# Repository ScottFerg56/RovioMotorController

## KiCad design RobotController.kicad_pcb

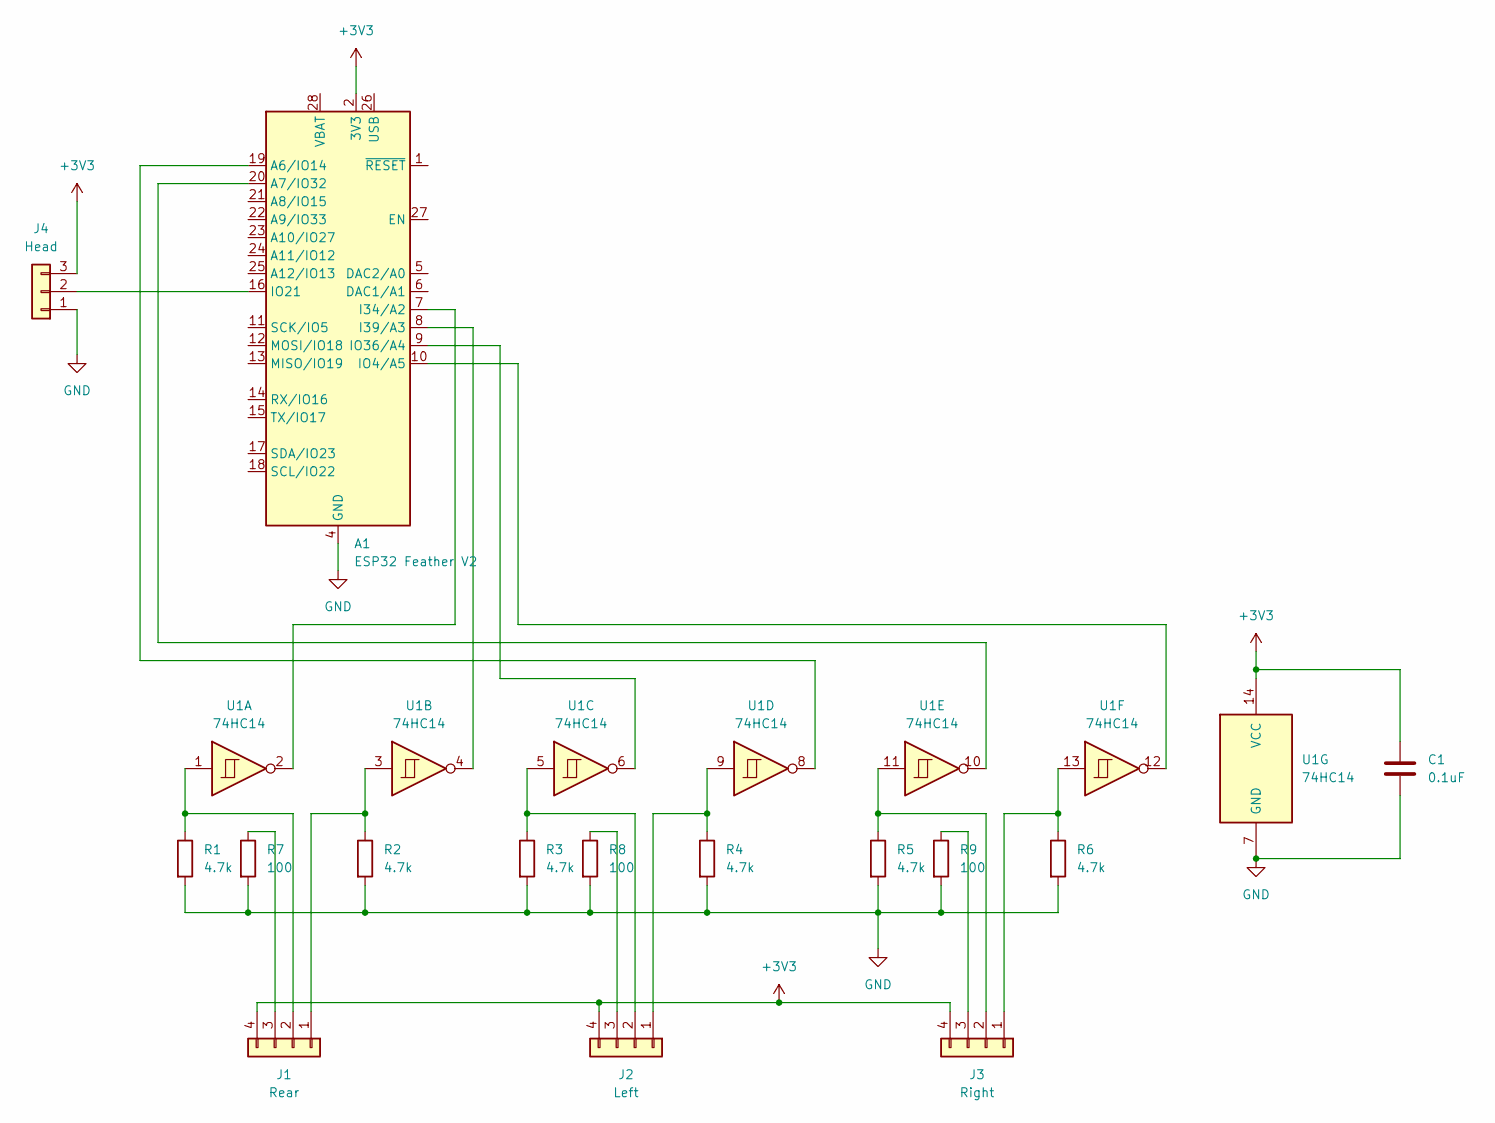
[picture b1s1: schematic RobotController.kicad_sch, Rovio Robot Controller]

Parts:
A1: ESP32 Feather V2; Adafruit_Feather
C1: 0.1uF; C_0805_2012Metric_Pad1.18x1.45mm_HandSolder
J1: Rear; JST_PH_B4B-PH-K_1x04_P2.00mm_Vertical
J2: Left; JST_PH_B4B-PH-K_1x04_P2.00mm_Vertical
J3: Right; JST_PH_B4B-PH-K_1x04_P2.00mm_Vertical
J4: Head; JST_PH_B3B-PH-K_1x03_P2.00mm_Vertical
R1, R2, R3, R4, R5, R6: 4.7k; R_0805_2012Metric_Pad1.20x1.40mm_HandSolder
R7, R8, R9: 100; R_0805_2012Metric_Pad1.20x1.40mm_HandSolder
U1: 74HC14; SOIC-14_3.9x8.7mm_P1.27mm

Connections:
+3V3: A1.2 (3V3), C1.1, J1.4, J2.4, J3.4, J4.3, U1.14 (VCC)
GND: A1.4 (GND), C1.2, J4.1, R1.2, R2.2, R3.2, R4.2, R5.2, R6.2, R7.2, R8.2, R9.2, U1.7 (GND)
unnamed: A1.19 (A6/IO14), U1.8
unnamed: A1.20 (A7/IO32), U1.10
unnamed: A1.7 (I34/A2), U1.2
unnamed: A1.8 (I39/A3), U1.4
unnamed: A1.10 (IO4/A5), U1.12
unnamed: A1.16 (IO21), J4.2
unnamed: A1.9 (IO36/A4), U1.6
unnamed: J1.1, R2.1, U1.3
unnamed: J1.2, R1.1, U1.1
unnamed: J1.3, R7.1
unnamed: J2.1, R4.1, U1.9
unnamed: J2.2, R3.1, U1.5
unnamed: J2.3, R8.1
unnamed: J3.1, R6.1, U1.13
unnamed: J3.2, R5.1, U1.11
unnamed: J3.3, R9.1

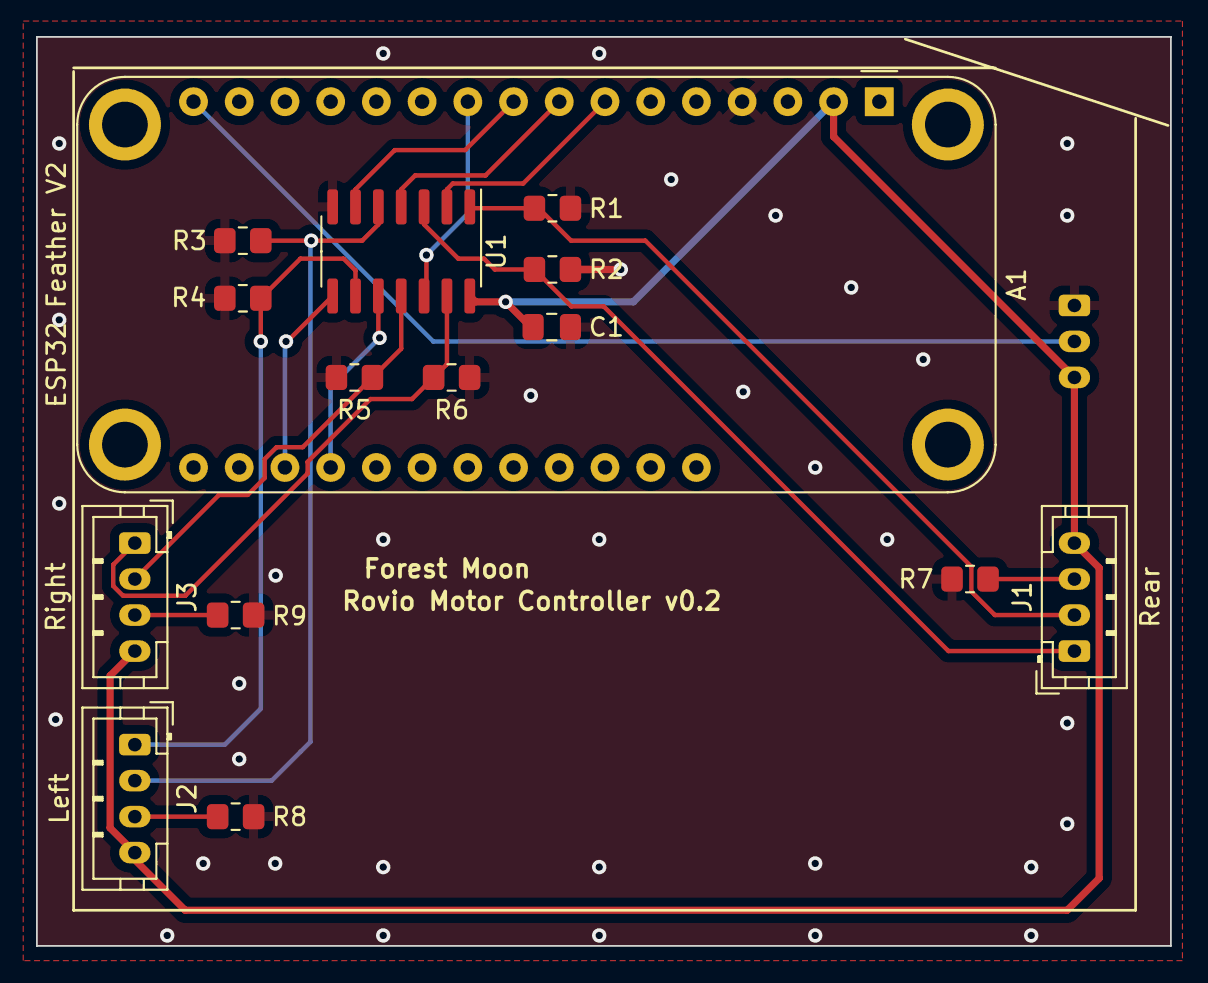
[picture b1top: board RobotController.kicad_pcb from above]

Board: 2 copper layers, 63.0 x 50.5 mm, 16 parts (1 on the bottom side), 18 nets.

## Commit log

2023-12-15 version 0.1
2023-12-15 start version 0.2
2023-12-15 courtyard exclusions
2025-03-28 kicad updates
